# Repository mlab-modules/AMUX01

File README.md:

# AMUX01 - four channel analog multiplexer

A simple module based on the MAX4734. The MAX4734 has 4 analog channels, controlled by signals A0, A1 and EN. Supports power supply and signals in the range of 1.6-3.6 V.

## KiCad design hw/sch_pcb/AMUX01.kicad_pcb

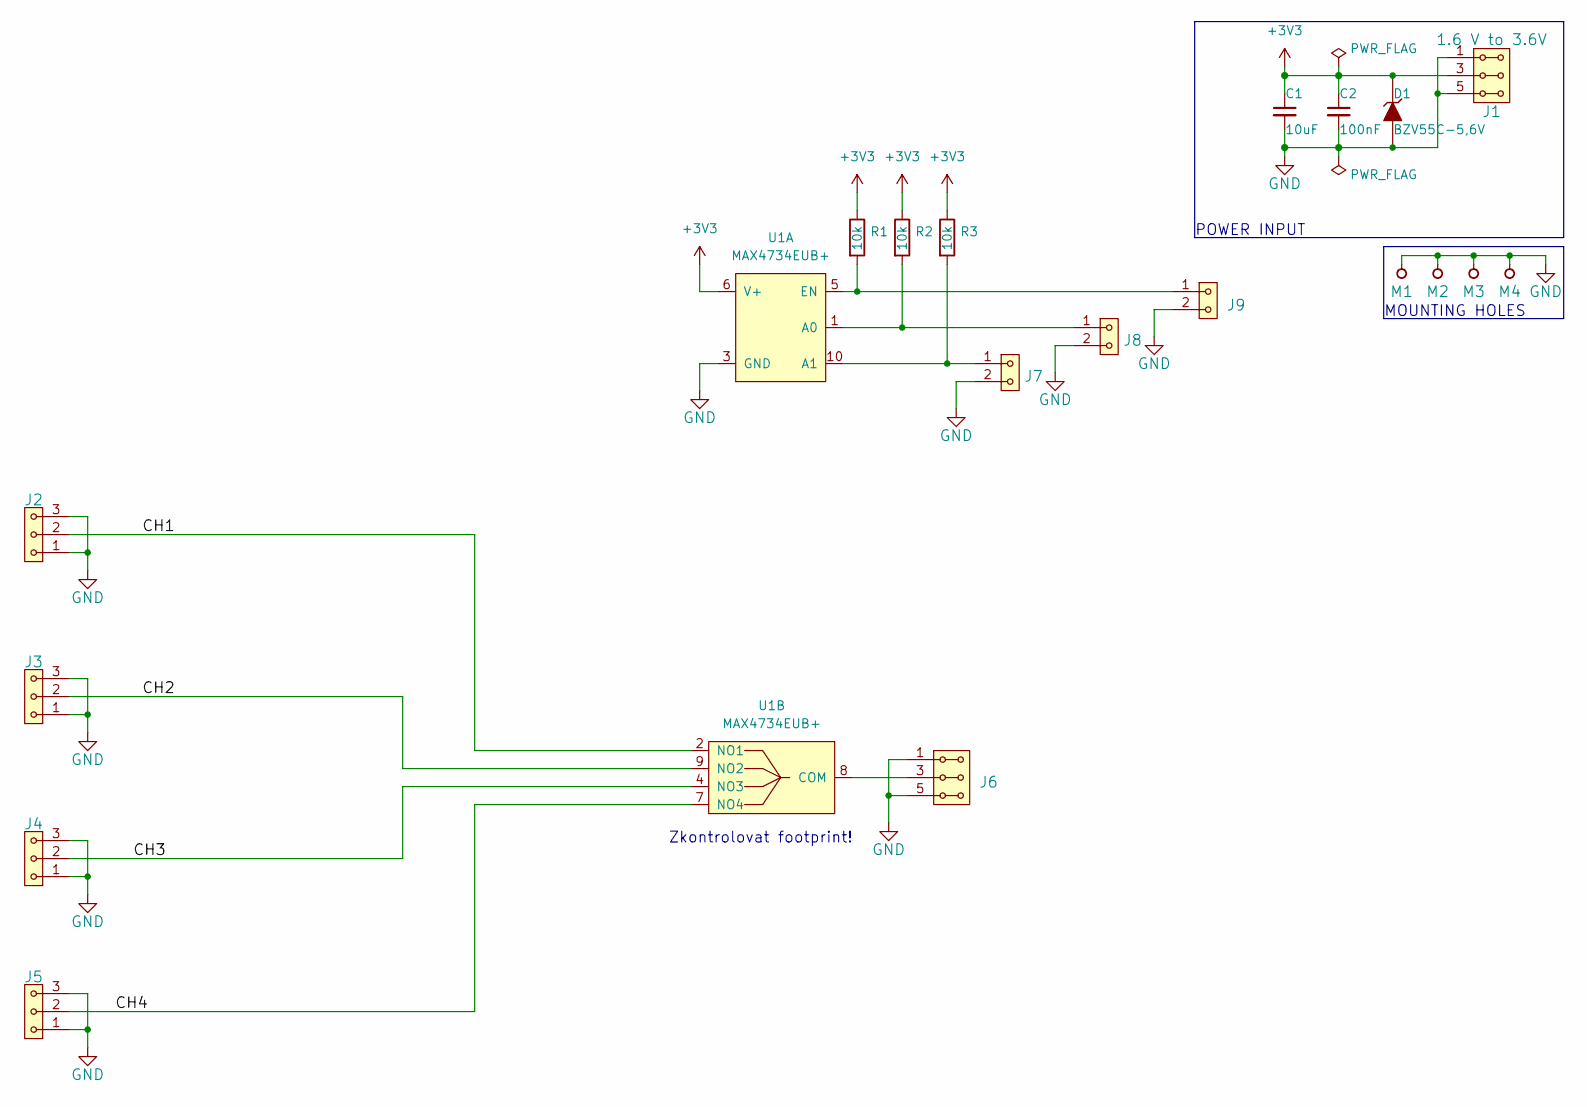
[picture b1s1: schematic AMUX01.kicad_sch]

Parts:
C1: 10uF; C_0805_2012Metric
C2: 100nF; C_0805_2012Metric
D1: BZV55C-5,6V; D_SMA
J1: 1.6 V to 3.6V; Straight_2x03
J2, J3, J4, J5: HEADER_1x03; Straight_1x03
J6: HEADER_2x03_PARALLEL; Straight_2x03
J7, J8, J9: HEADER_1x02; Straight_2x01
M1, M2: HOLE M3; MountingHole_3mm
M3, M4: HOLE; MountingHole_3mm
R1, R2, R3: 10k; R_0805_2012Metric
U1: MAX4734EUB+; MSOP-10_3x3mm_P0.5mm

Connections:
+3V3: C1.1, C2.1, D1.1 (K), J1.3, J1.4, R1.1, R2.1, R3.1, U1.6 (V+)
/CH1: J2.2, U1.2 (NO1)
/CH2: J3.2, U1.9 (NO2)
/CH3: J4.2, U1.4 (NO3)
/CH4: J5.2, U1.7 (NO4)
GND: C1.2, C2.2, D1.2 (A), J1.1, J1.2, J1.5, J1.6, J2.1, J2.3, J3.1, J3.3, J4.1, J4.3, J5.1, J5.3, J6.1, J6.2, J6.5, J6.6, J7.2, J8.2, J9.2, M1.1, M2.1, M3.1, M4.1, U1.3 (GND)
unnamed: J6.3, J6.4, U1.8 (COM)
unnamed: J7.1, R3.2, U1.10 (A1)
unnamed: J8.1, R2.2, U1.1 (A0)
unnamed: J9.1, R1.2, U1.5 (EN)

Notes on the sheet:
POWER INPUT
MOUNTING HOLES
Zkontrolovat footprint!

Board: 2 copper layers, 20 parts (7 on the bottom side), 10 nets, no tracks yet.

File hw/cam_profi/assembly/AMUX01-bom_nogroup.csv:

Component,Description,Part,References,Value,Footprint,Quantity Per PCB,Datasheet,ust_id
1,,C_Small-Device-ISM02A-rescue,C2,100nF,C_0805_2012Metric,1,,5c70984812875079b91f8bf2
2,,C_Small-Device-ISM02A-rescue,C1,10uF,C_0805_2012Metric,1,,5c70984812875079b91f8bbe
3,,D_ZENER-MLAB_D,D1,"BZV55C-5,6V",D_SMA,1,,5c70984512875079b91f88b2
4,"2x03 2.54 mm pitch header, 2 pins next to each other are connected",HEADER_2x03_PARALLEL,J1,1.6 V to 3.6V,Straight_2x03,1,,
5,1x02 2.54 mm pitch header,HEADER_1x02,J7J8J9,HEADER_1x02,Straight_2x01,3,,
6,1x03 2.54 mm pitch header,HEADER_1x03,J2J3J4J5,HEADER_1x03,Straight_1x03,4,,
7,"2x03 2.54 mm pitch header, 2 pins next to each other are connected",HEADER_2x03_PARALLEL,J6,HEADER_2x03_PARALLEL,Straight_2x03,1,,
8,Resistor,R,R1R2R3,10k,R_0805_2012Metric,3,~,
9,,MAX4734EUB+,U1,MAX4734EUB+,MSOP-10_3x3mm_P0.5mm,1,https://www.analog.com/media/en/technical-documentation/data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,

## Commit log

2023-02-09 The first multiplexer schematics.
2023-02-09 Add the link to datasheet.
2023-02-09 Change address setup. Use script to make module layout. Update PCB from schematics.
2023-02-09 Move origin to left bottom by script.
2023-02-10 Update GitHub actions.
2023-02-10 Update actions products
2023-02-11 Update workflow files
2023-02-12 Update metadata files
2023-05-25 automated commit; add github actions
2023-07-05 automated commit; rename source files to new naming convence
2023-09-16 Update image to image_title
2023-09-16 Update status
